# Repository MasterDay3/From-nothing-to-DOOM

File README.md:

<h1 align="center">Second-year Computer Science students, Applied Sciences Faculty, Ukrainian Catholic University (UCU)</h1>

<table>
  <tr>
    <td align="center" width="25%">
      
      <h3>@MasterDay3</h3>
    </td>
    <td align="center" width="25%">
      
      <h3>Oleksandr Vlasiuk</h3>
      <a href="https://github.com/chasyuk">@chasyuk</a>
    </td>
    <td align="center" width="25%">
      
      <h3>Anton Vertyporokh</h3>
      <a href="https://github.com/2surfff">@2surfff</a>
    </td>
    <td align="center" width="25%">
      
      <h3>Maksym Kyba</h3>
      <a href="https://github.com/Maksym-Kyba">@Maksym-Kyba</a>
    </td>
  </tr>
</table>

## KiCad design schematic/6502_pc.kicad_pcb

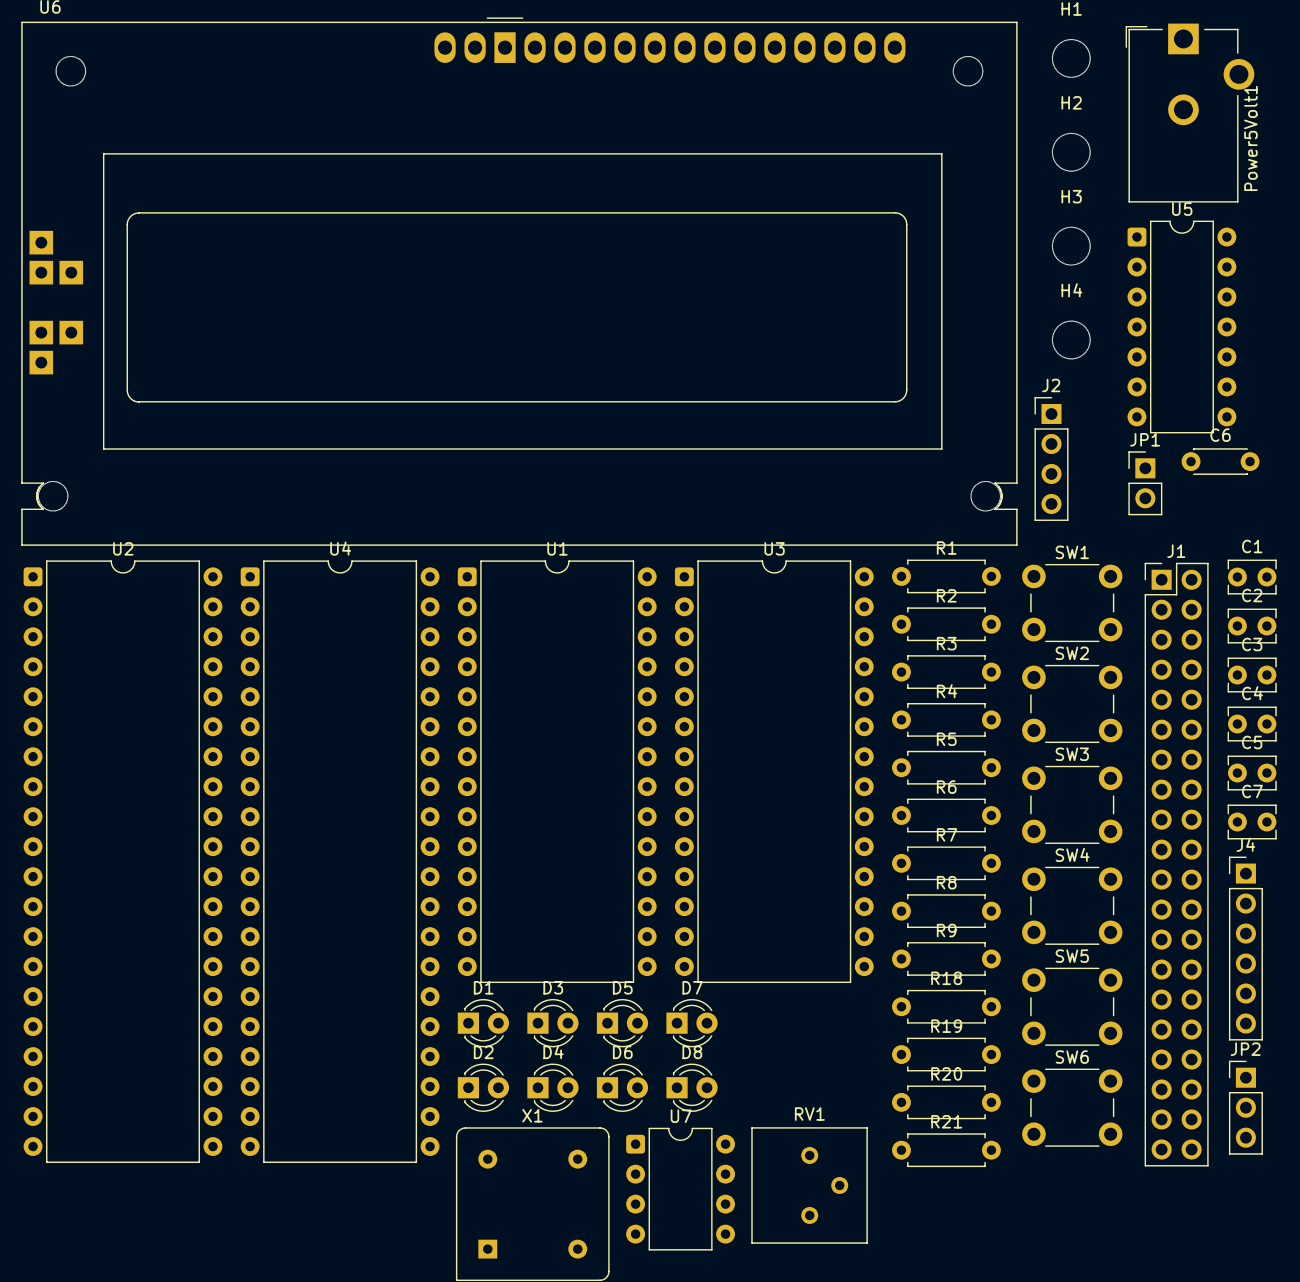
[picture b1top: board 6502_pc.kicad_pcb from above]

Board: 2 copper layers, 53 parts (0 on the bottom side), 60 nets, no tracks yet.

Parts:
C1, C2, C3, C4, C5, C7: 100nF; C_Disc_D3.8mm_W2.6mm_P2.50mm
C6: 220nF; C_Disc_D4.3mm_W1.9mm_P5.00mm
D1, D2, D3, D4, D5, D6, D7, D8: LED; LED_D3.0mm
H1, H2, H3, H4: MountingHole_3.2mm_M3
J1: PinHeader_2x20_P2.54mm_Vertical
J2: CLOCK_SEL; PinHeader_1x04_P2.54mm_Vertical
J4: Control; PinHeader_1x06_P2.54mm_Vertical
JP1: LED_EN; PinHeader_1x02_P2.54mm_Vertical
JP2: LCD_EN; PinHeader_1x03_P2.54mm_Vertical
Power5Volt1: Barrel_Jack; BarrelJack_CUI_PJ-102AH_Horizontal
R1, R2, R3, R18: 3k3; R_Axial_DIN0207_L6.3mm_D2.5mm_P7.62mm_Horizontal
R4, R5, R6, R7, R8, R9, R21: 1k; R_Axial_DIN0207_L6.3mm_D2.5mm_P7.62mm_Horizontal
R19: 220; R_Axial_DIN0207_L6.3mm_D2.5mm_P7.62mm_Horizontal
R20: 47k; R_Axial_DIN0207_L6.3mm_D2.5mm_P7.62mm_Horizontal
RV1: 10K; Potentiometer_Bourns_3386P_Vertical
SW1: RESET; SW_PUSH_6mm
SW2: MIDDLE; SW_PUSH_6mm
SW3: UP; SW_PUSH_6mm
SW4: DOWN; SW_PUSH_6mm
SW5: LEFT; SW_PUSH_6mm
SW6: RIGHT; SW_PUSH_6mm
U1: HM62256BLP; DIP-28_W15.24mm
U2: W65C02SxP; DIP-40_W15.24mm
U3: 28C256; DIP-28_W15.24mm
U4: W65C22SxP; DIP-40_W15.24mm
U5: 74HC00; DIP-14_W7.62mm
U6: RC1602A
U7: NE555P; DIP-8_W7.62mm
X1: 1MHZ; Oscillator_DIP-8

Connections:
/A0: J1.16, U1.10 (A0), U2.9 (A0), U3.10 (A0), U4.38 (RS0)
/A1: J1.15, U1.9 (A1), U2.10 (A1), U3.9 (A1), U4.37 (RS1)
/A2: J1.14, U1.8 (A2), U2.11 (A2), U3.8 (A2), U4.36 (RS2)
/A3: J1.13, U1.7 (A3), U2.12 (A3), U3.7 (A3), U4.35 (RS3)
/A4: J1.12, U1.6 (A4), U2.13 (A4), U3.6 (A4)
/A5: J1.11, U1.5 (A5), U2.14 (A5), U3.5 (A5)
/A6: J1.10, U1.4 (A6), U2.15 (A6), U3.4 (A6)
/A7: J1.9, U1.3 (A7), U2.16 (A7), U3.3 (A7)
/A8: J1.8, U1.25 (A8), U2.17 (A8), U3.25 (A8)
/A9: J1.7, U1.24 (A9), U2.18 (A9), U3.24 (A9)
/A10: J1.6, U1.21 (A10), U2.19 (A10), U3.21 (A10)
/A11: J1.5, U1.23 (A11), U2.20 (A11), U3.23 (A11)
/A12: J1.4, U1.2 (A12), U2.22 (A12), U3.2 (A12)
/A13: J1.3, U1.26 (A13), U2.23 (A13), U3.26 (A13), U4.24 (CS1)
/A14: J1.2, U1.1 (A14), U1.22 (~OE), U2.24 (A14), U3.1 (A14), U5.5
/A15: J1.1, U2.25 (A15), U5.12, U5.13
/BE: J1.21, R18.1, U2.36 (BE)
/D0: J1.27, U1.11 (Q0), U2.33 (D0), U3.11 (D0), U4.33 (D0)
/D1: J1.28, U1.12 (Q1), U2.32 (D1), U3.12 (D1), U4.32 (D1)
/D2: J1.29, U1.13 (Q2), U2.31 (D2), U3.13 (D2), U4.31 (D2)
/D3: J1.30, U1.15 (Q3), U2.30 (D3), U3.15 (D3), U4.30 (D3)
/D4: J1.31, U1.16 (Q4), U2.29 (D4), U3.16 (D4), U4.29 (D4)
/D5: J1.32, U1.17 (Q5), U2.28 (D5), U3.17 (D5), U4.28 (D5)
/D6: J1.33, U1.18 (Q6), U2.27 (D6), U3.18 (D6), U4.27 (D6)
/D7: J1.34, U1.19 (Q7), U2.26 (D7), U3.19 (D7), U4.26 (D7)
/IRQ: J1.22, R2.1, U2.4 (~IRQ), U4.21 (~IRQ)
/NMI: J1.23, R3.1, U2.6 (~NMI)
/PA0: J4.6, R5.2, SW2.1, U4.2 (PA0)
/PA1: J4.5, R6.2, SW3.1, U4.3 (PA1)
/PA2: J4.4, R7.2, SW4.1, U4.4 (PA2)
/PA3: J4.3, R8.2, SW5.1, U4.5 (PA3)
/PA4: J4.2, R9.2, SW6.1, U4.6 (PA4)
/PA5: U4.7 (PA5), U6.4 (RS)
/PA6: U4.8 (PA6), U6.5 (R/W)
/PA7: JP2.1, U4.9 (PA7)
/PB0: D1.2 (A), U4.10 (PB0), U6.7 (DB0)
/PB1: D2.2 (A), U4.11 (PB1), U6.8 (DB1)
/PB2: D3.2 (A), U4.12 (PB2), U6.9 (DB2)
/PB3: D4.2 (A), U4.13 (PB3), U6.10 (DB3)
/PB4: D5.2 (A), U4.14 (PB4), U6.11 (DB4)
/PB5: D6.2 (A), U4.15 (PB5), U6.12 (DB5)
/PB6: D7.2 (A), U4.16 (PB6), U6.13 (DB6)
/PB7: D8.2 (A), U4.17 (PB7), U6.14 (DB7)
/RDY: J1.25, R1.1, U2.2 (RDY)
/R_W: J1.24, U1.27 (~WE), U2.34 (R/~W), U4.22 (R/~W)
/SYNC: J1.26, U2.7 (SYNC)
CLOCK: J1.19, R19.1, U2.37 (ϕ0), U4.25 (ϕ2), U5.9
GND: C1.2, C2.2, C3.2, C4.2, C5.2, C6.2, C7.2, J1.17, J2.1, J4.1, JP1.1, Power5Volt1.2, R20.2, RV1.1, SW2.2, SW3.2, SW4.2, SW5.2, SW6.2, U1.14 (GND), U2.21 (VSS), U3.14 (GND), U3.22 (~OE), U4.1 (VSS), U5.1, U5.2, U5.7 (GND), U6.1 (VSS), U6.16 (K), U7.1 (GND), X1.4 (GND)
unnamed: D1.1 (K), D2.1 (K), D3.1 (K), D4.1 (K), D5.1 (K), D6.1 (K), D7.1 (K), D8.1 (K), JP1.2
unnamed: J2.2, R19.2
unnamed: J2.3, X1.5 (OUT)
unnamed: JP2.2, U6.6 (E)
unnamed: R20.1, R21.1, SW1.2
unnamed: RV1.2, U6.3 (VO)
unnamed: C6.1, R21.2, U7.2 (TRIG), U7.6 (THRES)
RAM: U1.20 (~CS), U5.8
RESET: J1.20, R4.2, U2.40 (~RES), U4.34 (~RES), U7.7 (DISCH)
ROM: U3.20 (~CS), U5.4, U5.10, U5.11
VCC: C1.1, C2.1, C3.1, C4.1, C5.1, C7.1, J1.18, J2.4, JP2.3, Power5Volt1.1, R1.2, R2.2, R3.2, R4.1, R5.1, R6.1, R7.1, R8.1, R9.1, R18.2, SW1.1, U1.28 (VCC), U2.8 (VDD), U3.27 (~WE), U3.28 (VCC), U4.20 (VCC), U5.14 (VCC), U6.2 (VDD), U6.15 (A/VEE), U7.4 (~RST), U7.8 (VCC), X1.8 (Vcc)
VIA: U4.23 (~CS2), U5.6
